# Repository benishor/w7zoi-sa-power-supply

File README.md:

# w7zoi-sa-power-supply
Dual 15V power supply for W7ZOI spectrum analyzer project

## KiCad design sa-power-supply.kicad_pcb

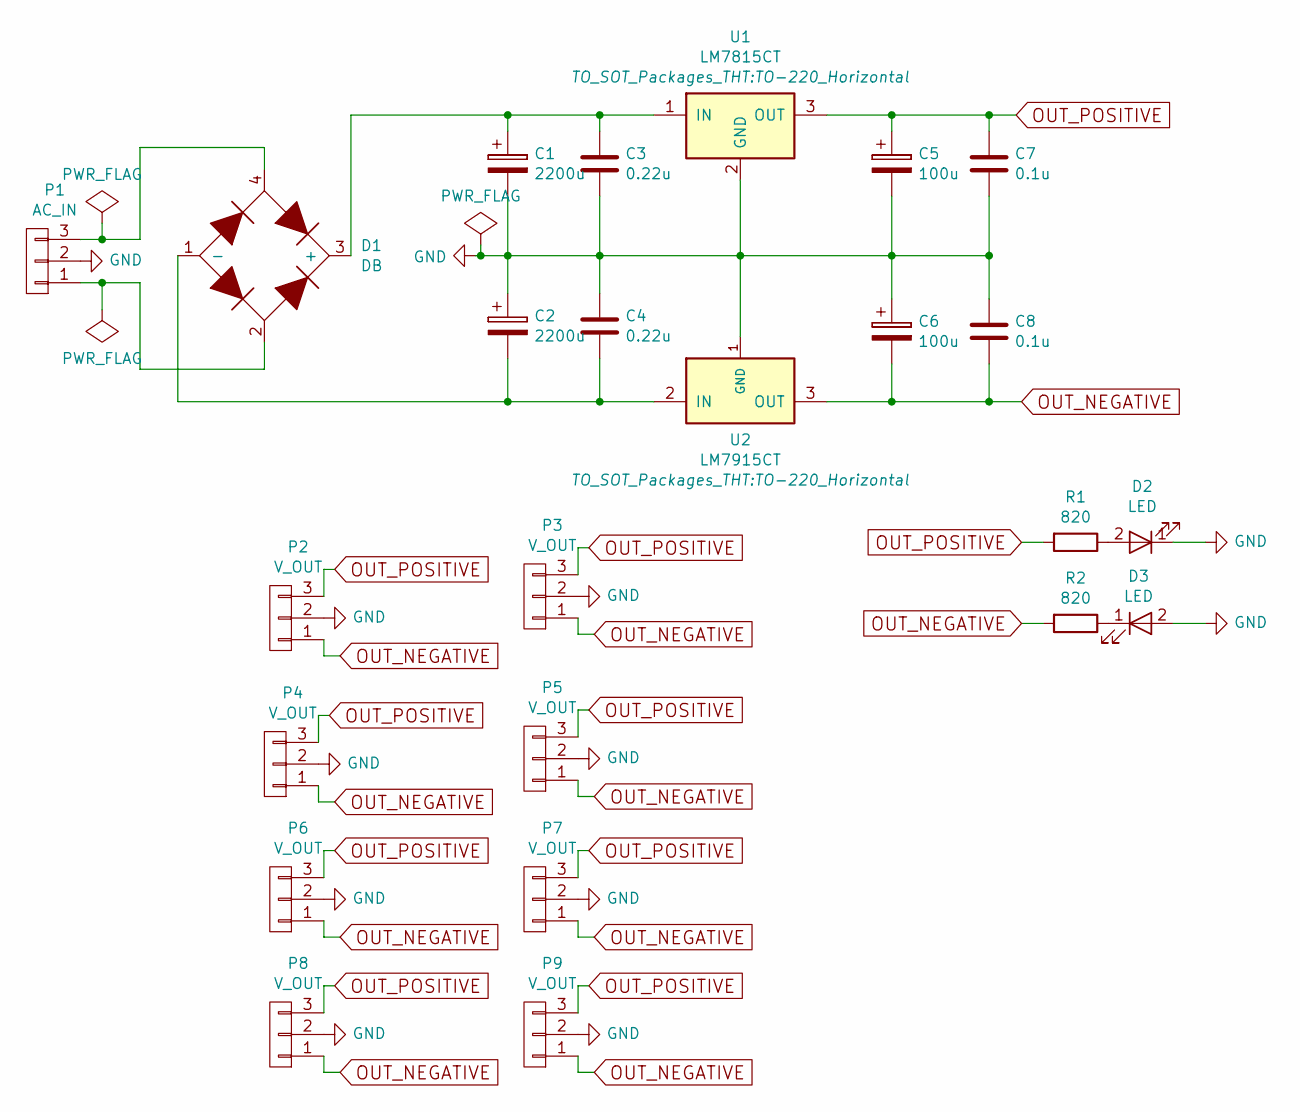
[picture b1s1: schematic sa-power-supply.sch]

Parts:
C1, C2: 2200u; CP_Radial_D17.0mm_P7.50mm
C3, C4: 0.22u; C_Disc_D7.5mm_W5.0mm_P7.50mm
C5, C6: 100u; CP_Radial_D7.5mm_P2.50mm
C7, C8: 0.1u; C_Disc_D7.5mm_W5.0mm_P7.50mm
D1: DB; Diode_Bridge_18.5x5.5
D2, D3: LED; LED_D5.0mm
P1: AC_IN; Pin_Header_Straight_1x03_Pitch2.54mm
P2, P3, P4, P5, P6, P7, P8, P9: V_OUT; Pin_Header_Straight_1x03_Pitch2.54mm
R1, R2: 820; R_Axial_DIN0207_L6.3mm_D2.5mm_P7.62mm_Horizontal
U1: LM7815CT; TO-220_Horizontal
U2: LM7915CT; TO-220_Horizontal

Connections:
GND: C1.2, C2.1, C3.2, C4.1, C5.2, C6.1, C7.2, C8.1, D2.1 (K), D3.2 (A), P1.2, P2.2, P3.2, P4.2, P5.2, P6.2, P7.2, P8.2, P9.2, U1.2 (GND), U2.1 (GND)
unnamed: C1.1, C3.1, D1.3 (+), U1.1 (IN)
unnamed: C2.2, C4.2, D1.1 (-), U2.2 (IN)
unnamed: D1.2, P1.1
unnamed: D1.4, P1.3
unnamed: D2.2 (A), R1.1
unnamed: D3.1 (K), R2.1
OUT_NEGATIVE: C6.2, C8.2, P2.1, P3.1, P4.1, P5.1, P6.1, P7.1, P8.1, P9.1, R2.2, U2.3 (OUT)
OUT_POSITIVE: C5.1, C7.1, P2.3, P3.3, P4.3, P5.3, P6.3, P7.3, P8.3, P9.3, R1.2, U1.3 (OUT)

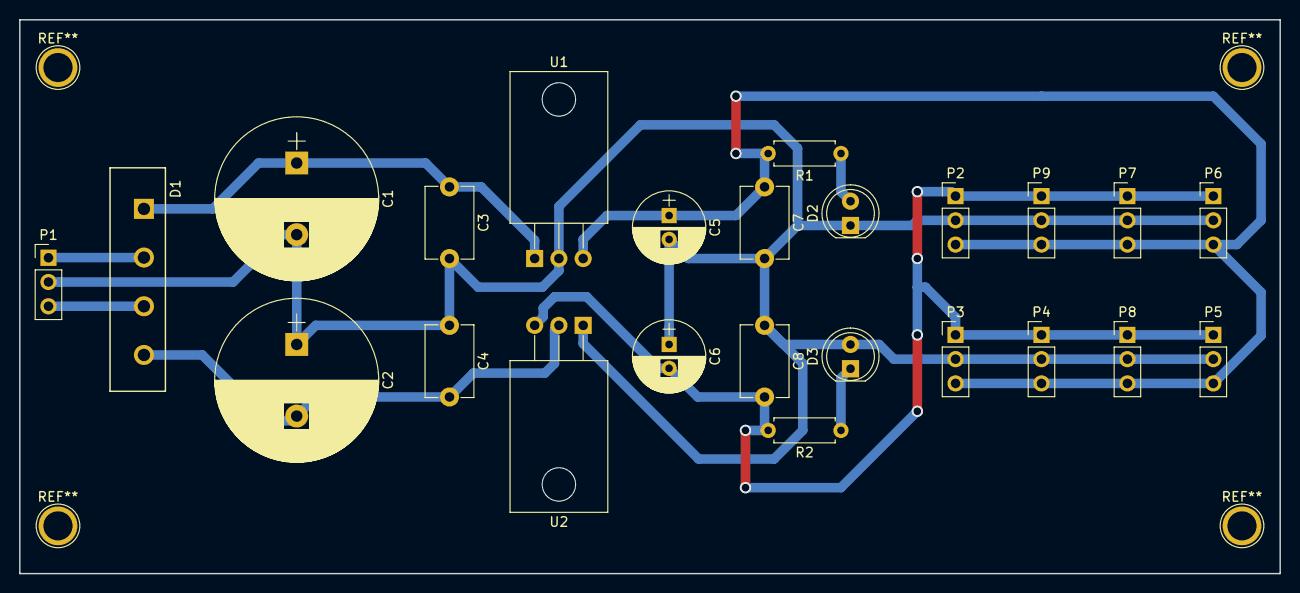
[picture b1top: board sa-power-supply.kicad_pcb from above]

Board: 2 copper layers, 132.0 x 58.0 mm, 24 parts (0 on the bottom side), 9 nets.

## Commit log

2017-03-17 Initial import
